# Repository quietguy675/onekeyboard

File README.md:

# onekeyboard
Spiritual counterpart to the techkeys onekeyboard

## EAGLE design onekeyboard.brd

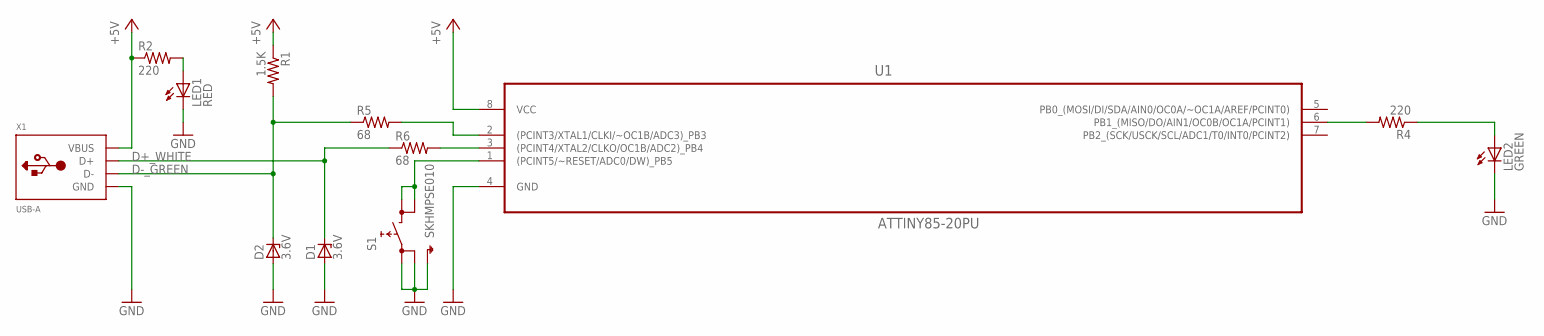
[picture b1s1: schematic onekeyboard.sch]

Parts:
D1, D2: 3.6V; DO41Z10
LED1: RED; LED5MM
LED2: GREEN; LED5MM
R1: 1.5K; 0204/5
R2, R4: 220; 0204/5
R5, R6: 68; R0402
S1: SKHMPSE010; SKHMPXE010
U1: ATTINY85-20PU; DIP254P762X533-8
X1: USB-A; MOLEX_480371000

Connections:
+5V: R1.1, R2.1, U1.8 (VCC), X1.1 (VBUS)
D+_WHITE: D1.C, R6.1, X1.3 (D+)
D-_GREEN: D2.C, R1.2, R5.1, X1.2 (D-)
GND: D1.A, D2.A, LED1.K (C), LED2.K (C), S1.1 (1.1), S1.2 (1.2), S1.5 (SH), U1.4 (GND), X1.4 (GND)
unnamed: R5.2, U1.2 ((PCINT3/XTAL1/CLKI/~OC1B/ADC3)_PB3)
unnamed: R6.2, U1.3 ((PCINT4/XTAL2/CLKO/OC1B/ADC2)_PB4)
unnamed: S1.3 (2.1), S1.4 (2.2), U1.1 ((PCINT5/~RESET/ADC0/DW)_PB5)
unnamed: R4.2, U1.6 (PB1_(MISO/DO/AIN1/OC0B/OC1A/PCINT1))
unnamed: LED2.A, R4.1
unnamed: LED1.A, R2.2

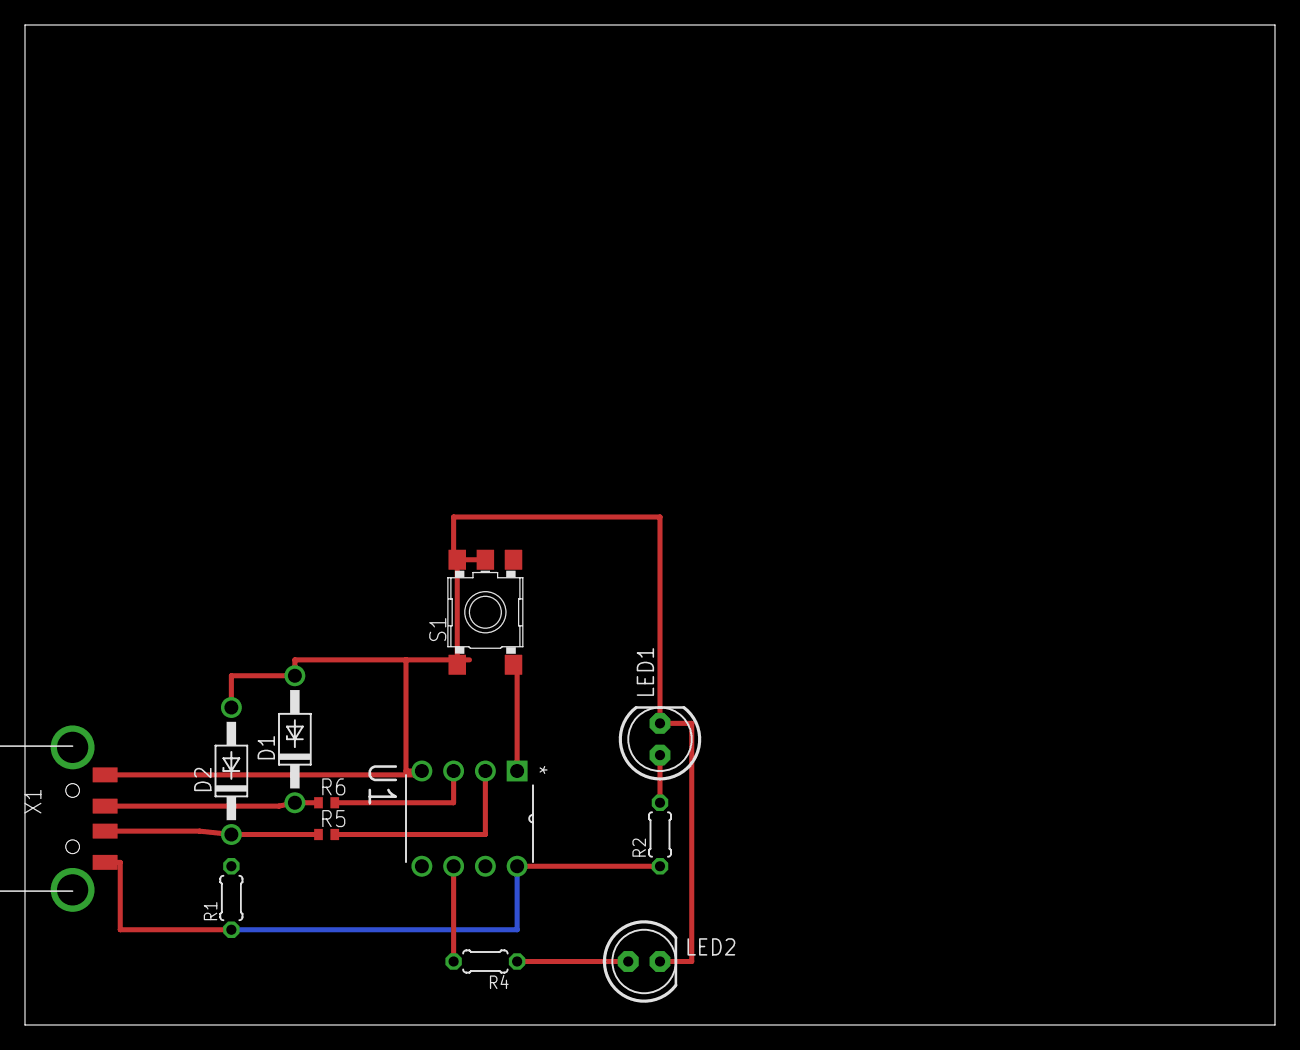
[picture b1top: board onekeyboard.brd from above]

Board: 2 copper layers, 100.0 x 80.0 mm, 12 parts (0 on the bottom side), 10 nets.

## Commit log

2017-01-05 Added schematic and board layout
